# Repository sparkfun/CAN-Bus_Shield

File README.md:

SparkFun CAN-Bus Shield
==============

[*SparkFun CAN-BUS Shield (DEV-13262)*](https://www.sparkfun.com/products/13262)

This shield give the Arduino CAN-BUS capability. 

Repository Contents
-------------------

* **/Hardware** - Eagle design files (.brd, .sch)
* **/Libraries** - Libraries for use with the CAN-Bus Shield. 
* **/Production** - Production panel files (.brd)

Documentation
--------------
* **[Library](https://github.com/sparkfun/SparkFun_CAN-Bus_Arduino_Library)** - Arduino library for the CAN-Bus.
* **[Hookup Guide](https://learn.sparkfun.com/tutorials/can-bus-shield-hookup-guide)** - Basic hookup guide for the CAN-Bus.
* **[SparkFun Fritzing repo](https://github.com/sparkfun/Fritzing_Parts)** - Fritzing diagrams for SparkFun products.
* **[SparkFun 3D Model repo](https://github.com/sparkfun/3D_Models)** - 3D models of SparkFun products. 

Product Versions
----------------
* [DEV-13262](https://www.sparkfun.com/products/13262)- Version 1.3. Currently live. 
* [DEV-10039](https://www.sparkfun.com/products/retired/10039)- Version 1.2. Retired. 

GitHub Version History
---------------
* [V1.3](https://github.com/sparkfun/CAN-Bus_Shield/tree/v1.3) - This is version 1.3 of the shield. Currently live.
* [V1.2](https://github.com/sparkfun/CAN-Bus_Shield/tree/v1.2) - This is version 1.2 of the shield. Retired

License Information
-------------------

This product is _**open source**_! 

Please review the LICENSE.md file for license information. 

If you have any questions or concerns on licensing, please contact techsupport@sparkfun.com.

Distributed as-is; no warranty is given.

- Your friends at SparkFun.

This is a collaboration with SK Pang Electronics. A portion of each sale goes back to them for product support and continued development.

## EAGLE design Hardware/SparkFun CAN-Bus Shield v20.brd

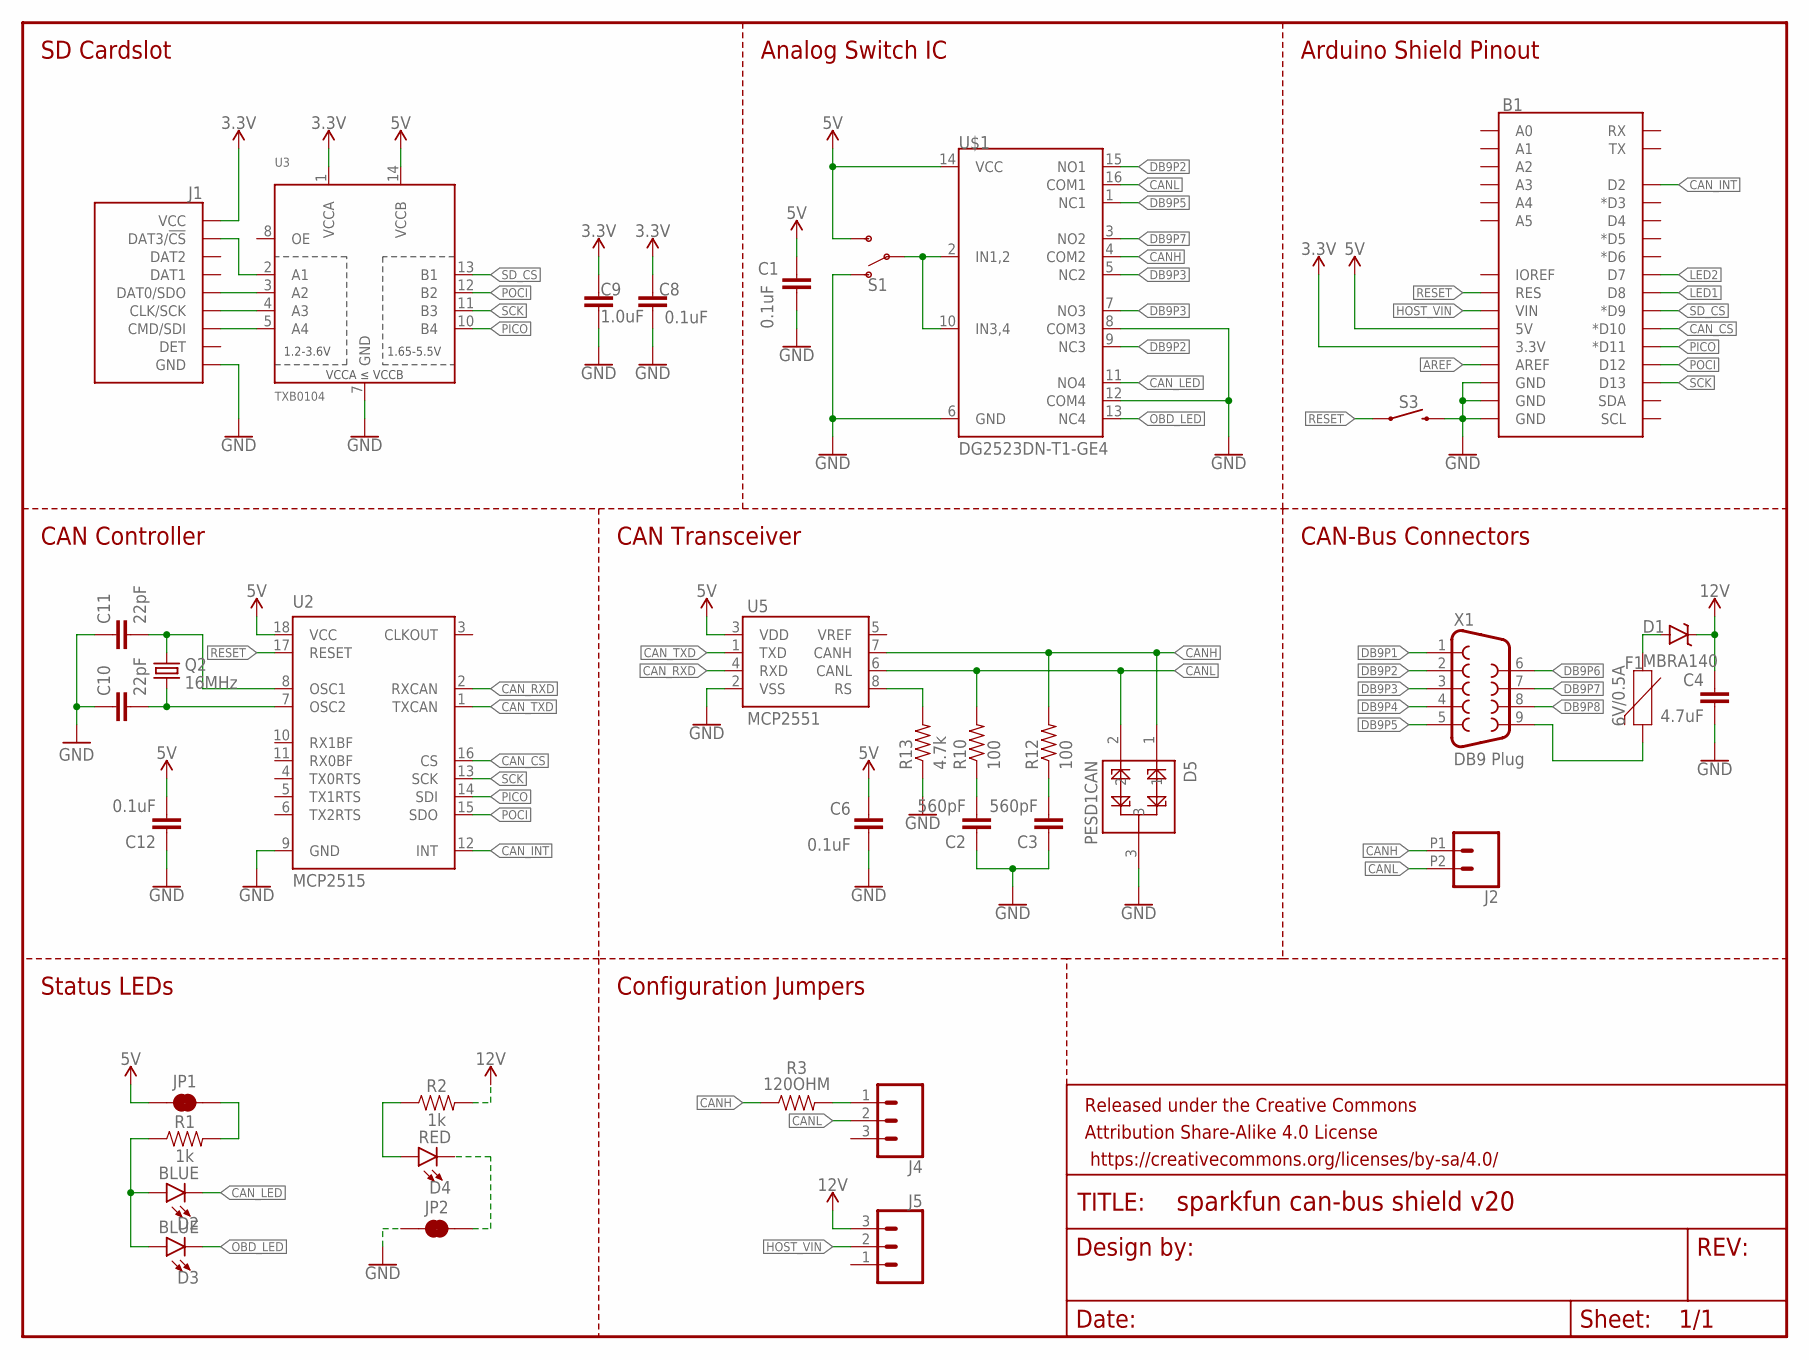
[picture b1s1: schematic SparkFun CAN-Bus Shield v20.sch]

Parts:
B1: ARDUINO_UNO_R3_SHIELDUNO_R3_SHIELD_LOCK; UNO_R3_SHIELD_LOCK
C1, C6, C8, C12: 0.1uF; 0603
C2, C3: 560pF; 0603
C4: 4.7uF; 0603
C9: 1.0uF; 0603
C10, C11: 22pF; 0603
D1: MBRA140; SMA-DIODE
D2, D3: BLUE; LED-0603
D4: RED; LED-0603
D5: PESD1CAN; SOT23-3
F1: 6V/0.5A; 1206
FRAME1: FRAME-LETTER; CREATIVE_COMMONS
J1: MICRO-SD-PUSH-PUSH-EXT-PIN; MICROSD-EXTERNALPIN
J2: CONN_022.54MM_SCREWTERM; 1X02_2.54_SCREWTERM
J4, J5: CONN_031X03_NO_SILK; 1X03_NO_SILK
JP1, JP2: JUMPER-SMT_2_NC_TRACE_NO-SILK; SMT-JUMPER_2_NC_TRACE_NO-SILK
Q2: 16MHz; CRYSTAL-SMD-5X3.2-4PAD
R1, R2: 1k; 0603
R3: 120OHM; 0603
R10, R12: 100; 0603
R13: 4.7k; 0603
S1: SWITCH-SPDT-SMD-AYZ0202; SWITCH_DPDT_SMD_AYZ0202
S3: MOMENTARY-SWITCH-SPST-SMD-5.2-TALL-REDUNDANT; TACTILE_SWITCH_SMD_5.2MM
U2: MCP2515; SO18W
U3: TXB0104; SO14
U5: MCP2551; SO08
U$1: DG2523DN-T1-GE4; QFN16-3X3MM_1:1_V03
X1: DB9 Plug; DB9_MALE

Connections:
3.3V: B1.3.3V, C8.2, C9.1, J1.4 (VCC), U3.1 (VCCA)
5V: B1.5V, C1.2, C6.2, C12.2, JP1.1, S1.3 (S), U2.18 (VCC), U3.14 (VCCB), U5.3 (VDD), U$1.14 (VCC)
12V: C4.1, D1.C, J5.3, R2.2
AREF: B1.AREF
CANH: D5.1, J2.P1 (1), R3.1, R12.2, U5.7 (CANH), U$1.4 (COM2)
CANL: D5.2, J2.P2 (2), J4.2, R10.2, U5.6 (CANL), U$1.16 (COM1)
CAN_CS: B1.D10 (*D10), U2.16 (CS)
CAN_INT: B1.D2, U2.12 (INT)
CAN_LED: D2.C, U$1.11 (NO4)
CAN_RXD: U2.2 (RXCAN), U5.4 (RXD)
CAN_TXD: U2.1 (TXCAN), U5.1 (TXD)
DB9P1: X1.1
DB9P2: U$1.9 (NC3), U$1.15 (NO1), X1.2
DB9P3: U$1.5 (NC2), U$1.7 (NO3), X1.3
DB9P4: X1.4
DB9P5: U$1.1 (NC1), X1.5
DB9P6: X1.6
DB9P7: U$1.3 (NO2), X1.7
DB9P8: X1.8
GND: B1.GND@0 (GND), B1.GND@1 (GND), B1.GND@2 (GND), C1.1, C2.1, C3.1, C4.2, C6.1, C8.1, C9.2, C10.1, C11.1, C12.1, D5.3, J1.6 (GND), J1.10 (GND), J1.11 (GND), J1.12 (GND), J1.13 (GND), JP2.1, R13.1, S3.3 (2), S3.4 (2), U2.9 (GND), U3.7 (GND), U5.2 (VSS), U$1.8 (COM3), U$1.12 (COM4)
HOST_VIN: B1.VIN, J5.2
LED1: B1.D8
LED2: B1.D7
unnamed: C11.2, Q2.3 (2), U2.8 (OSC1)
unnamed: C10.2, Q2.1, U2.7 (OSC2)
unnamed: J1.2 (DAT3/!CS!), U3.2 (A1)
unnamed: S1.1 (O), U$1.6 (GND)
unnamed: J1.7 (DAT0/SDO), U3.3 (A2)
unnamed: J1.5 (CLK/SCK), U3.4 (A3)
unnamed: J1.3 (CMD/SDI), U3.5 (A4)
unnamed: D4.A, R2.1
unnamed: C2.2, R10.1
unnamed: C3.2, R12.1
unnamed: JP1.2, R1.2
unnamed: D2.A, D3.A, R1.1
unnamed: F1.2, X1.9
unnamed: R13.2, U5.8 (RS)
unnamed: D4.C, JP2.2
unnamed: D1.A, F1.1
unnamed: J4.1, R3.2
unnamed: S1.2, U$1.2 (IN1,2), U$1.10 (IN3,4)
OBD_LED: D3.C, U$1.13 (NC4)
PICO: B1.D11 (*D11), U2.14 (SDI), U3.10 (B4)
POCI: B1.D12, U2.15 (SDO), U3.12 (B2)
RESET: B1.RES, S3.1, S3.2 (1), U2.17 (RESET)
SCK: B1.D13, U2.13 (SCK), U3.11 (B3)
SD_CS: B1.D9 (*D9), U3.13 (B1)

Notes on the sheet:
SD Cardslot
Analog Switch IC
Arduino Shield Pinout
CAN-Bus Connectors
CAN Transceiver
CAN Controller
Status LEDs
Configuration Jumpers

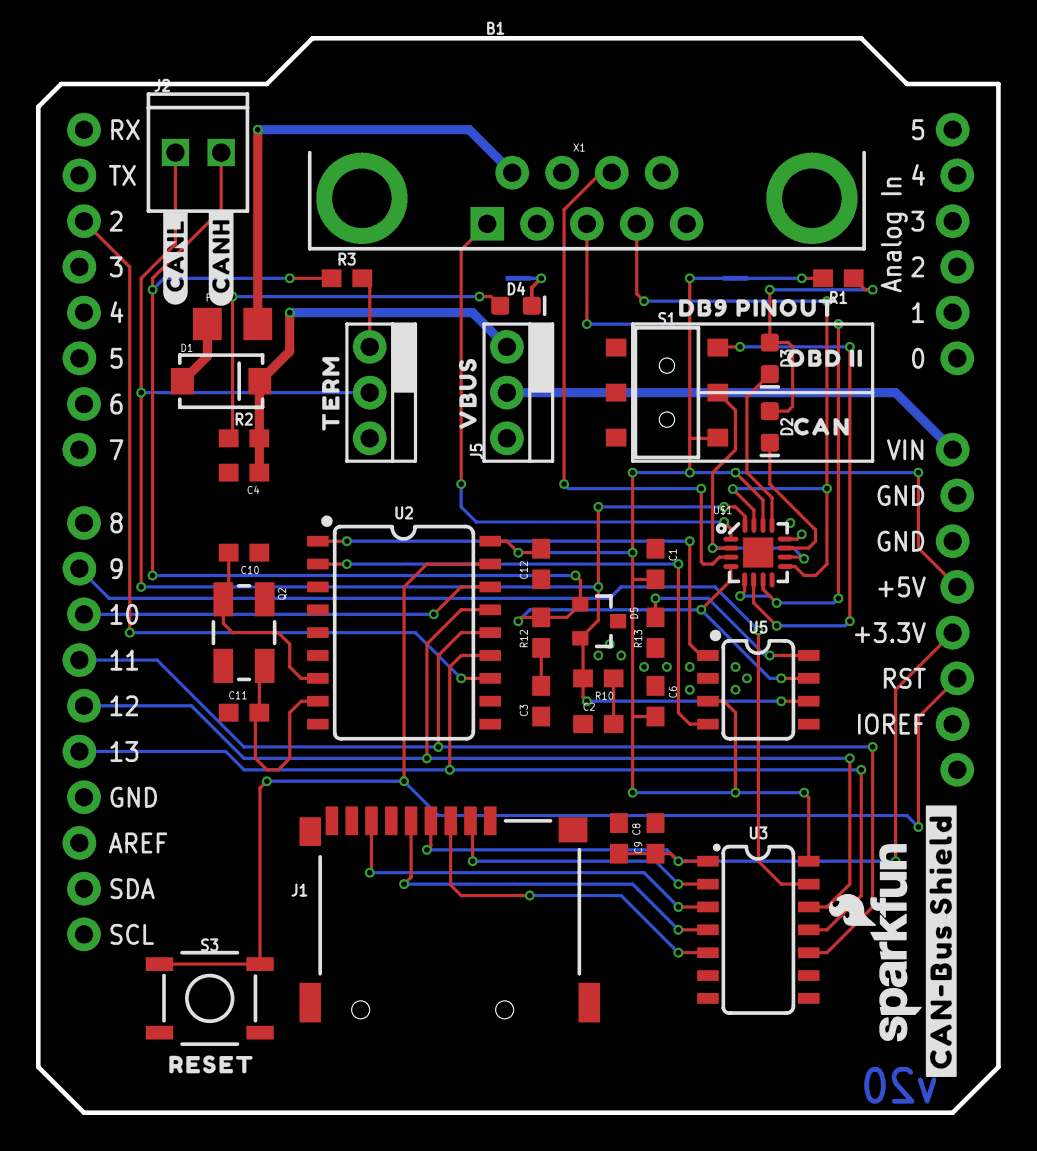
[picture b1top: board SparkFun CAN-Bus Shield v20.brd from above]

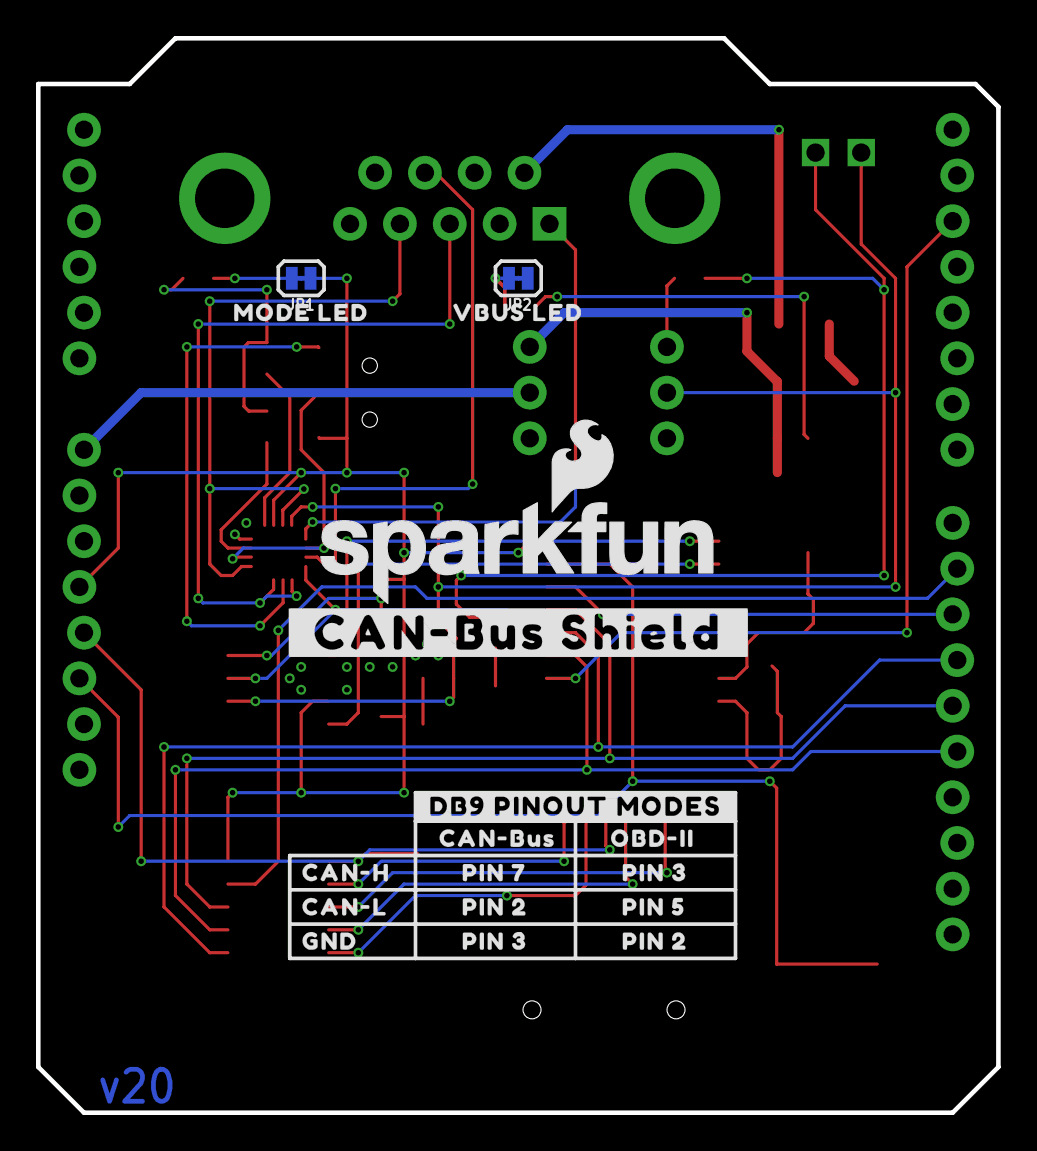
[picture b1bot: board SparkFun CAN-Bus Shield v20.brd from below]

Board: 2 copper layers, 53.3 x 59.7 mm, 64 parts (18 on the bottom side), 40 nets.

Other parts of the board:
U$2: TERM0
U$3: VBUS0
U$4: OBD_II0
U$5: CAN0
U$6: RESET0
U$7: DB9_PINOUT0
U$8: #CANH#0
U$9: #CANL#0
U$10: #CAN#BUS_SHIELD#0
U$11: SFE_LOGO_NAME_FLAME_.1
U$12: #_CAN#BUS_SHIELD_#0
U$13: SFE_LOGO_NAME_FLAME_.2
U$14: #DB9_PINOUT_MODES#0
U$15: CAN#H0
U$16: CAN#L0
U$17: GND0
U$18: CAN#BUS0
U$19: OBD#II0
U$20: PIN_70
U$21, U$22: PIN_20
U$23, U$24: PIN_30
U$25: PIN_50
U$26: MODE_LED0
U$27: VBUS_LED0

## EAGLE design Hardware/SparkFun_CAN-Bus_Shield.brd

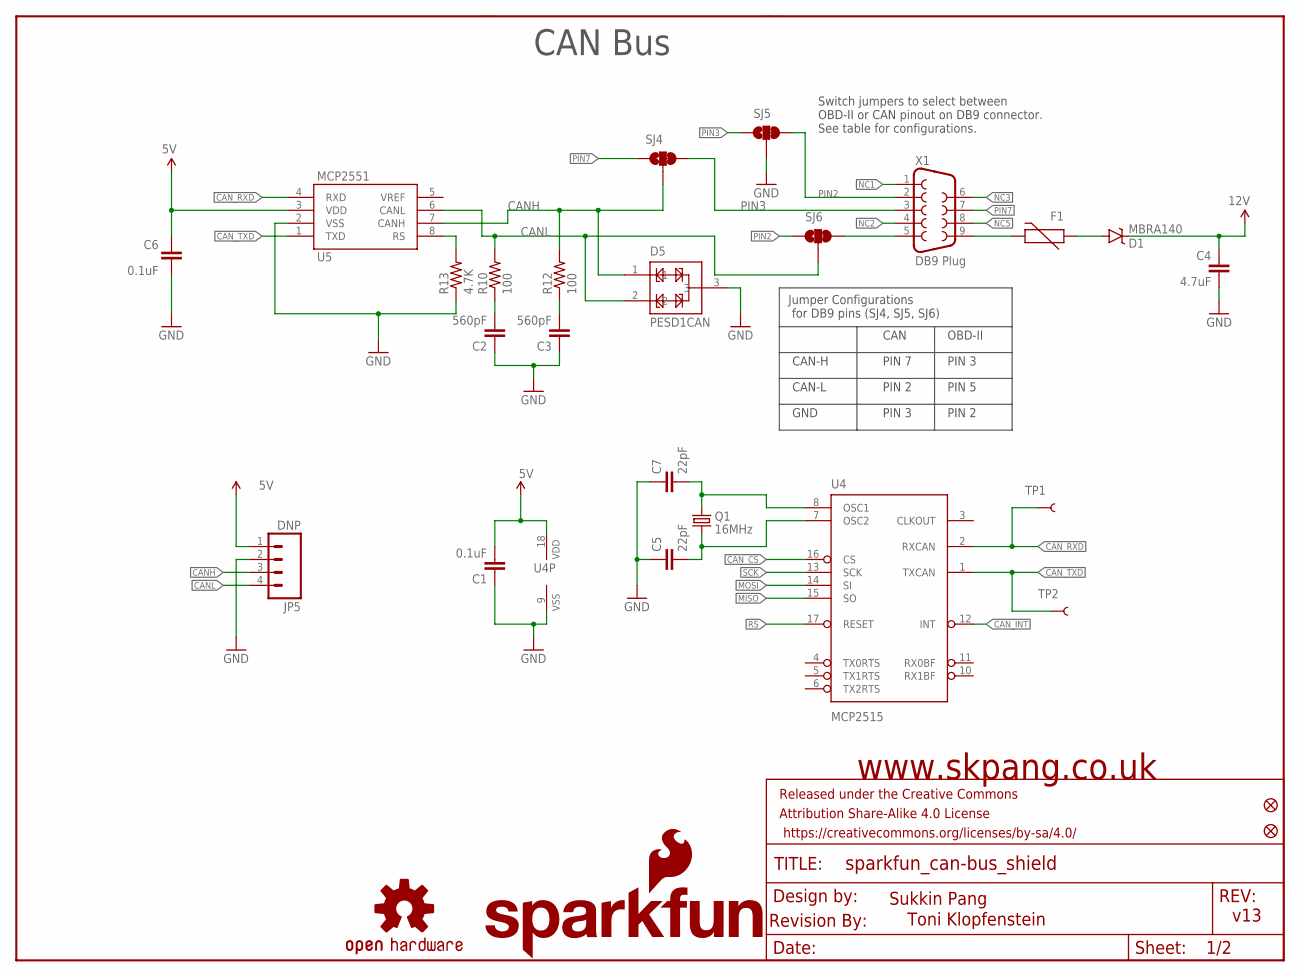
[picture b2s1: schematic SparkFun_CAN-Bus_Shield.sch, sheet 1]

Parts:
C1, C6: 0.1uF; 0603-CAP
C2, C3: 560pF; 0603-CAP
C4: 4.7uF; 0603-CAP
C5, C7: 22pF; 0603-CAP
D1: MBRA140; SMA-DIODE
D5: PESD1CAN; SOT23-3
F1: PTCTHERMISTOR1206; PTC-1206
FRAME1: FRAME-LETTER; CREATIVE_COMMONS
JP2, JP3: FIDUCIAL1X2; FIDUCIAL-1X2
JP4: SFE_LOGO_NAME_FLAME.1_INCH; SFE_LOGO_NAME_FLAME_.1
JP5: DNP; 1X04
LOGO1: OSHW-LOGOM; OSHW-LOGO-M
Q1: 16MHz; CRYSTAL-SMD-5X3
R10, R12: 100; 0603-RES
R13: 4.7K; 0603-RES
SJ4, SJ5, SJ6: JUMPER-PAD-3-2OF3_NC_BY_TRACE_SMALL; PAD-JUMPER-3-2OF3_NC_BY_TRACE_YES_SILK_FULL_BOX
TP1, TP2: TEST-POINT3X5; PAD.03X.05
U4: MCP2515; SO-18W
U5: MCP2551; SO08
U$1: REVISION
X1: DB9 Plug; DB9_MALE

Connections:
5V: C1.2, C6.2, JP5.1, U4.18 (VDD), U5.3 (VDD); also elsewhere on the board
12V: C4.1, D1.C; also elsewhere on the board
CANH: D5.1, JP5.3, R12.2, SJ4.2, U5.7 (CANH)
CANL: D5.2, JP5.4, R10.2, SJ6.2, U5.6 (CANL)
CAN_CS: U4.16 (CS); also elsewhere on the board
CAN_INT: U4.12 (INT); also elsewhere on the board
CAN_RXD: TP1.P$1, U4.2 (RXCAN), U5.4 (RXD)
CAN_TXD: TP2.P$1, U4.1 (TXCAN), U5.1 (TXD)
GND: C1.1, C2.1, C3.1, C4.2, C5.1, C6.1, C7.1, D5.3, JP5.2, R13.1, SJ5.2, U4.9 (VSS), U5.2 (VSS); also elsewhere on the board
MISO: U4.15 (SO); also elsewhere on the board
MOSI: U4.14 (SI); also elsewhere on the board
unnamed: SJ6.3, X1.5
unnamed: C2.2, R10.1
unnamed: C3.2, R12.1
unnamed: F1.2, X1.9
unnamed: R13.2, U5.8 (RS)
unnamed: D1.A, F1.1
unnamed: C7.2, Q1.3 (2), U4.8 (OSC1)
unnamed: C5.2, Q1.1, U4.7 (OSC2)
NC1: X1.1
NC2: X1.4
NC3: X1.6
NC5: X1.8
PIN2: SJ5.3, SJ6.1, X1.2
PIN3: SJ4.3, SJ5.1, X1.3
PIN7: SJ4.1, X1.7
RS: U4.17 (RESET); also elsewhere on the board
SCK: U4.13 (SCK); also elsewhere on the board

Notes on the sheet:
www.skpang.co.uk
Toni Klopfenstein
CAN Bus
CAN
OBD-II
CAN-H
CAN-L
GND
PIN 5
PIN 2
PIN 3
PIN 7
Jumper Configurations for DB9 pins (SJ4, SJ5, SJ6)
Switch jumpers to select between OBD-II or CAN pinout on DB9 connector. See table for configurations.
v13
Sukkin Pang

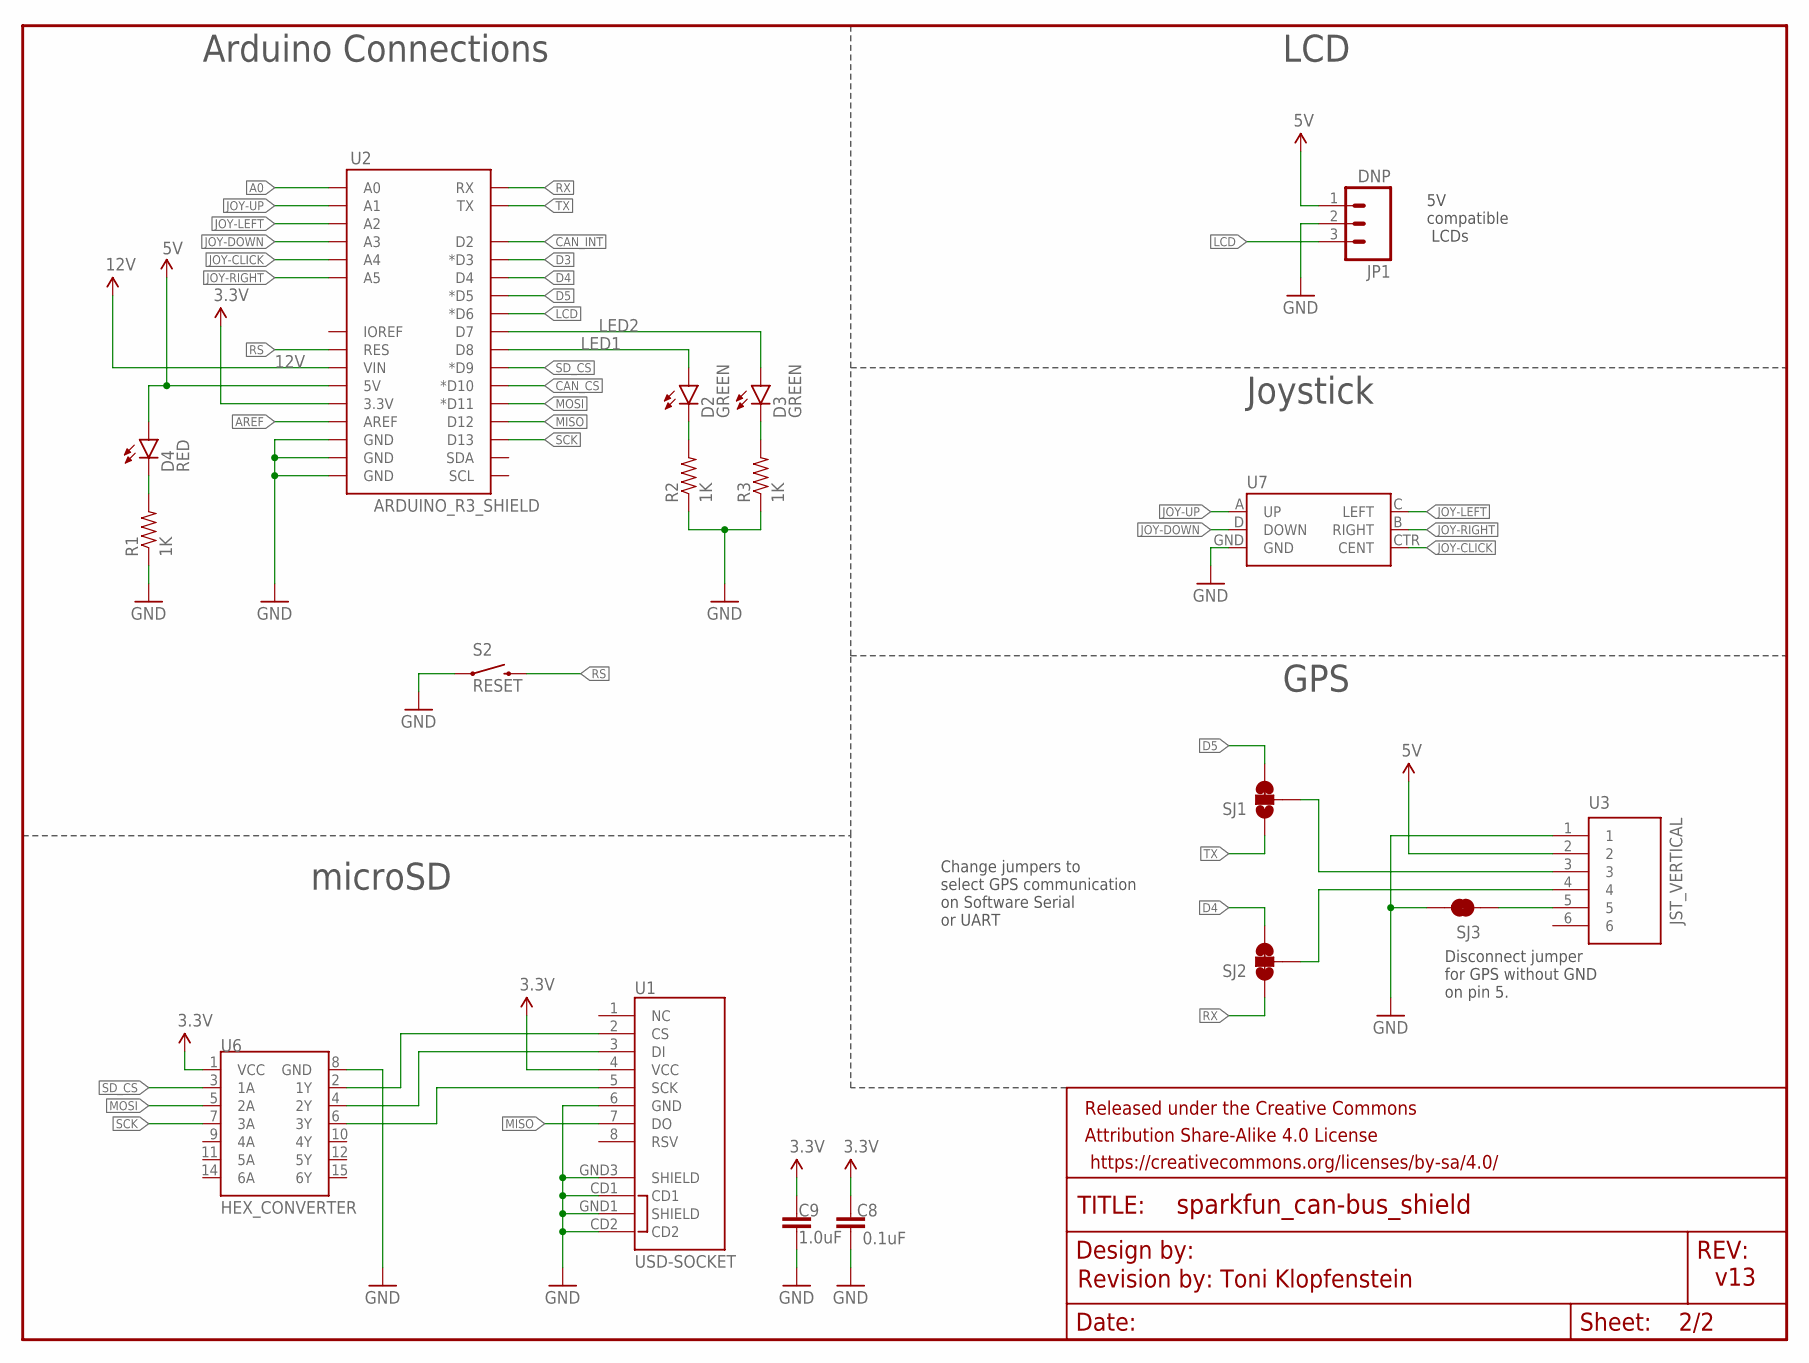
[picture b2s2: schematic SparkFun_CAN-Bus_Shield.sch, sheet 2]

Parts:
C8: 0.1uF; 0603-CAP
C9: 1.0uF; 0603-CAP
D2, D3: GREEN; LED-0603
D4: RED; LED-0603
FRAME2: FRAME-LETTERNO_PACKAGE; DUMMY
JP1: DNP; MOLEX-1X3_LOCK
R1, R2, R3: 1K; 0603-RES
S2: RESET; TACTILE-SWITCH-SMD
SJ1, SJ2: JUMPER-PAD-3-2OF3_NC_BY_TRACE_SMALL; PAD-JUMPER-3-2OF3_NC_BY_TRACE_YES_SILK_FULL_BOX
SJ3: JUMPER-PAD-2-NC_BY_TRACE; PAD-JUMPER-2-NC_BY_TRACE_YES_SILK
U1: USD-SOCKET; MICROSD_1:1
U2: ARDUINO_R3_SHIELD; UNO_R3_SHIELD
U3: JST_VERTICAL; JST-6-SMD-VERT-1.0MM
U6: HEX_CONVERTER; SO016
U7: JOYSTICK_MINI

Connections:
3.3V: C8.2, C9.1, U1.4 (VCC), U2.3.3V, U6.1 (VCC)
5V: D4.A, JP1.1, U2.5V, U3.2; also elsewhere on the board
12V: U2.VIN; also elsewhere on the board
A0: U2.A0
AREF: U2.AREF
CAN_CS: U2.D10 (*D10); also elsewhere on the board
CAN_INT: U2.D2; also elsewhere on the board
D3: U2.D3 (*D3)
D4: SJ2.3, U2.D4
D5: SJ1.3, U2.D5 (*D5)
GND: C8.1, C9.2, JP1.2, R1.1, R2.1, R3.1, S2.1, SJ3.2, U1.6 (GND), U1.CD1, U1.CD2, U1.GND1 (SHIELD), U1.GND3 (SHIELD), U2.GND@0 (GND), U2.GND@1 (GND), U2.GND@2 (GND), U3.1, U6.8 (GND), U7.GND; also elsewhere on the board
JOY-CLICK: U2.A4, U7.CTR (CENT)
JOY-DOWN: U2.A3, U7.D (DOWN)
JOY-LEFT: U2.A2, U7.C (LEFT)
JOY-RIGHT: U2.A5, U7.B (RIGHT)
JOY-UP: U2.A1, U7.A (UP)
LCD: JP1.3, U2.D6 (*D6)
LED1: D2.A, U2.D8
LED2: D3.A, U2.D7
MISO: U1.7 (DO), U2.D12; also elsewhere on the board
MOSI: U2.D11 (*D11), U6.5 (2A); also elsewhere on the board
unnamed: SJ3.1, U3.5
unnamed: D4.C, R1.2
unnamed: D2.C, R2.2
unnamed: D3.C, R3.2
unnamed: U1.2 (CS), U6.2 (1Y)
unnamed: U1.3 (DI), U6.4 (2Y)
unnamed: SJ1.2, U3.3
unnamed: SJ2.2, U3.4
unnamed: U1.5 (SCK), U6.6 (3Y)
RS: S2.3 (2), U2.RES; also elsewhere on the board
RX: SJ2.1, U2.RX
SCK: U2.D13, U6.7 (3A); also elsewhere on the board
SD_CS: U2.D9 (*D9), U6.3 (1A)
TX: SJ1.1, U2.TX

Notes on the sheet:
Arduino Connections
LCD
Joystick
5V compatible LCDs
GPS
Change jumpers to select GPS communication on Software Serial or UART
Disconnect jumper for GPS without GND on pin 5.
microSD
Revision by: Toni Klopfenstein
v13

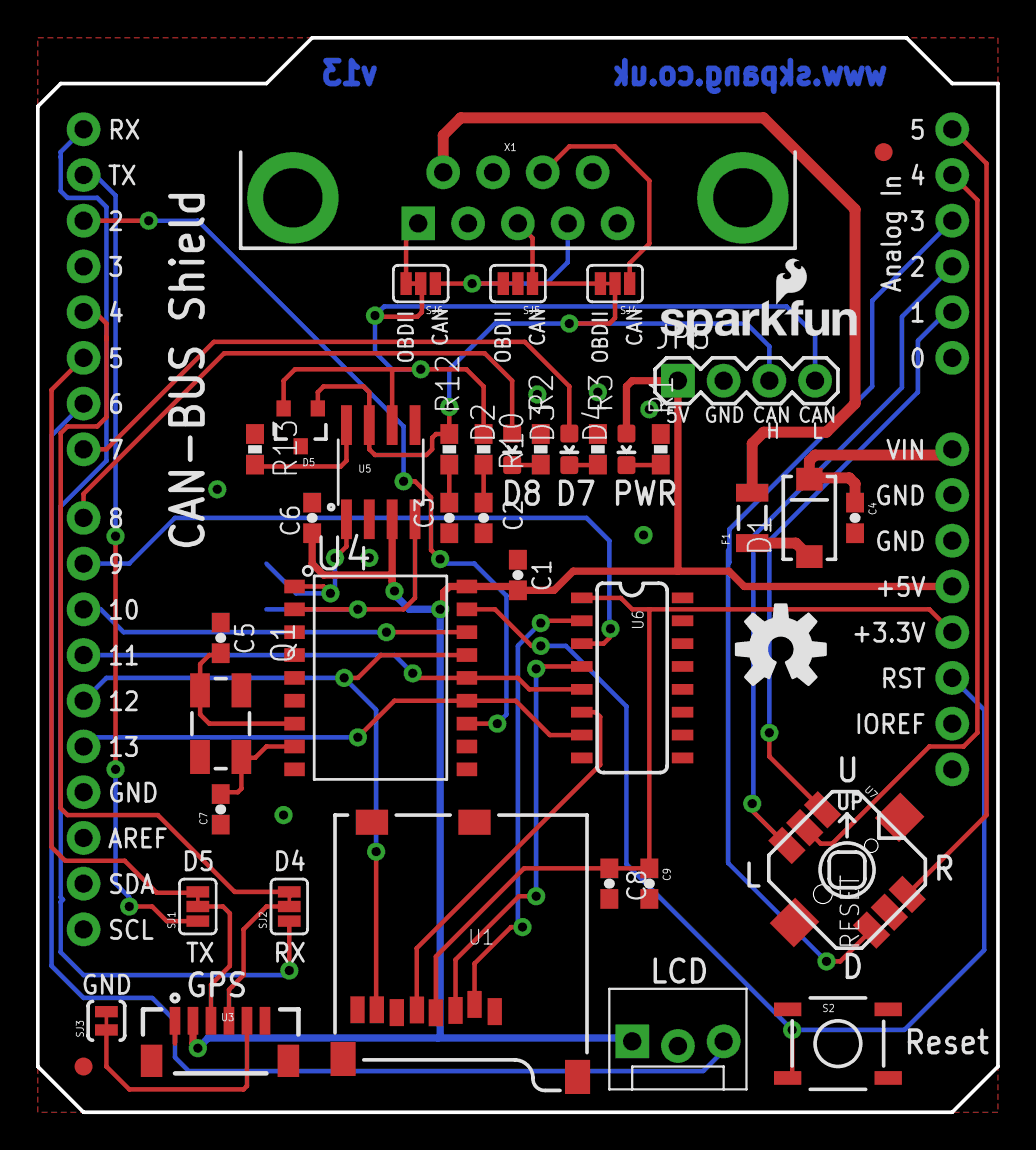
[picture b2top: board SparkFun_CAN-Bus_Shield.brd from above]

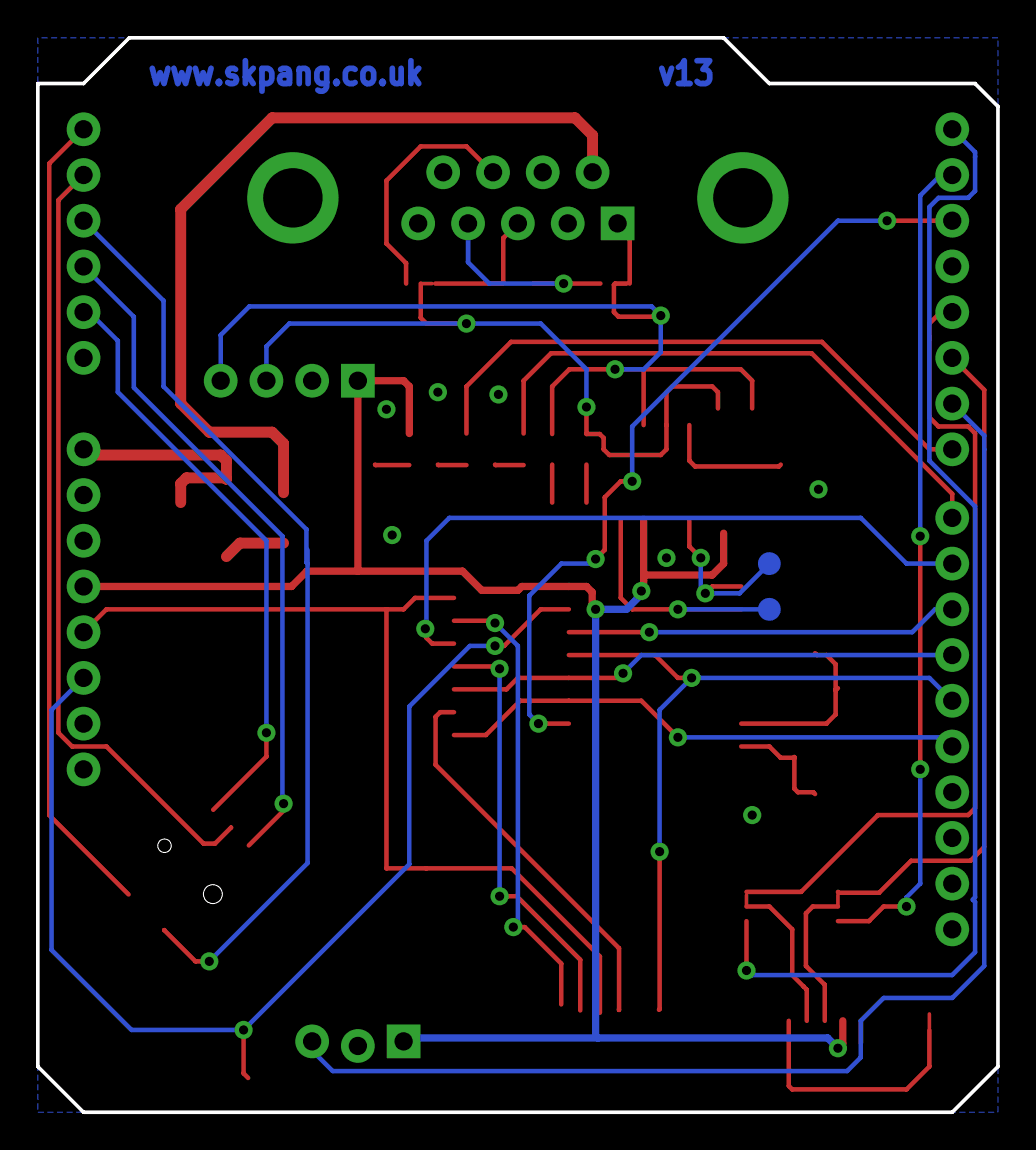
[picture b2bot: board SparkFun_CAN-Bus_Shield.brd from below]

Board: 2 copper layers, 53.3 x 59.7 mm, 48 parts (2 on the bottom side), 47 nets.

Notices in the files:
parts and their libraries:
SparkFun-Boards: Licensing: Creative Commons ShareAlike 4.0 International - https://creativecommons.org/licenses/by-sa/4.0
SparkFun-Aesthetics: Released under the Creative Commons Attribution Share-Alike 4.0 License
SparkFun-Aesthetics: https://creativecommons.org/licenses/by-sa/4.0
